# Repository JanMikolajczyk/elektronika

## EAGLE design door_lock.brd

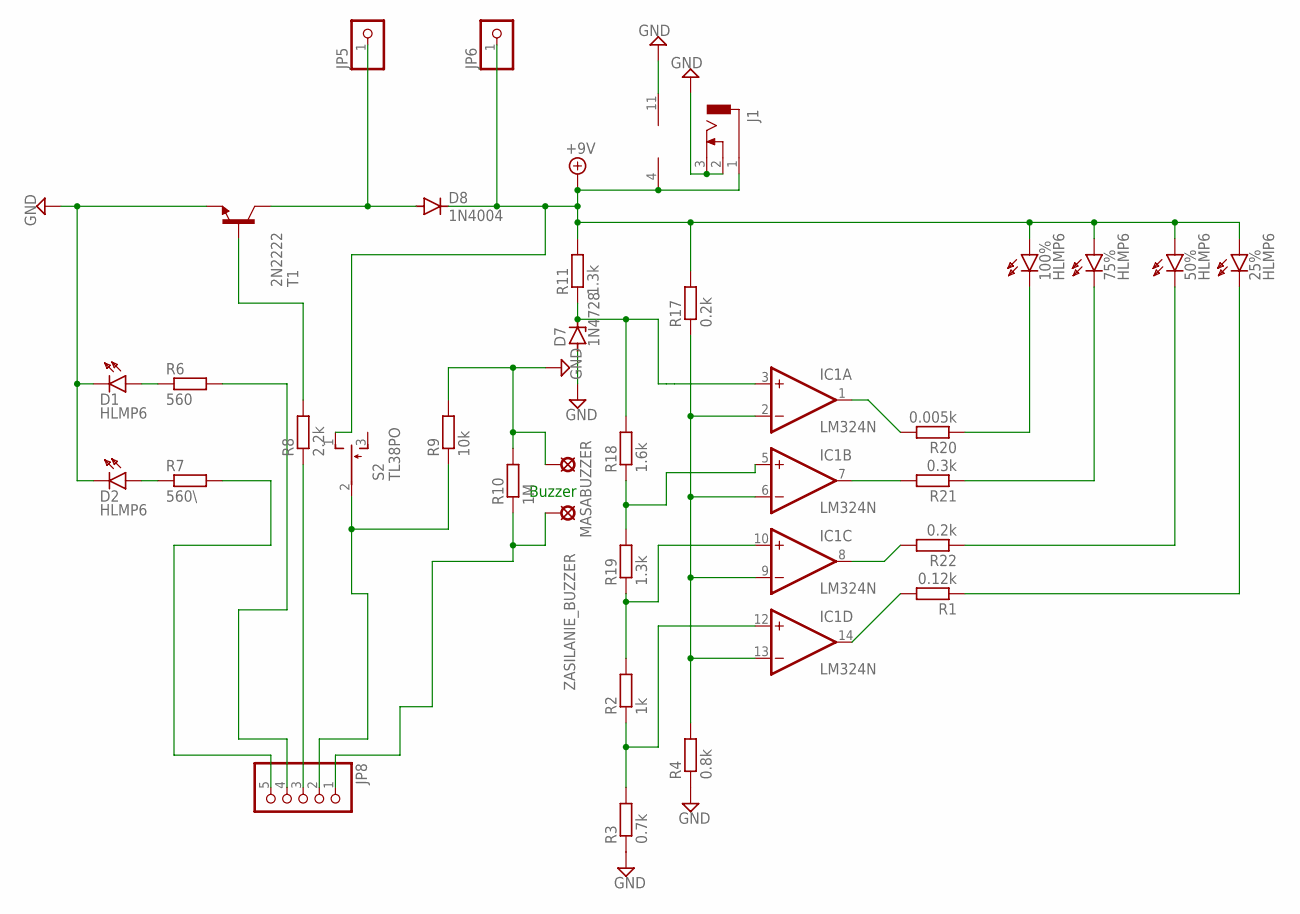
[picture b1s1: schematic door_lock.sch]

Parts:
25%, 50%, 75%, 100%: HLMP6
D1, D2: HLMP6
D7: 1N4728; DO41Z10
D8: 1N4004; DO41-10
IC1: LM324N; DIL14
J1: DCJ0303
JP5, JP6: PINHD-1X1; 1X01
JP8: PINHD-1X5; 1X05
MASABUZZER: LSP10
R1: 0.12k; 0207/10
R2: 1k; 0207/10
R3: 0.7k; 0207/10
R4: 0.8k; 0207/10
R6: 560; 0207/10
R7: 560\; 0207/10
R8: 2.2k; 0207/10
R9: 10k; 0207/10
R10: 1M; 0207/10
R11, R19: 1.3k; 0207/10
R17, R22: 0.2k; 0207/10
R18: 1.6k; 0207/10
R20: 0.005k; 0207/10
R21: 0.3k; 0207/10
S2: TL38PO; TL3XPO
T1: 2N2222; TO18
ZASILANIE_BUZZER: LSP10

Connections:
+9V: 25%.A, 50%.A, 75%.A, 100%.A, D8.C, IC1.4 (V+), J1.1, JP6.1, R11.2, R17.2, S2.1 (O)
GND: D1.K, D2.K, D7.A, IC1.11 (V-), J1.2, J1.3, MASABUZZER.MP, R3.1, R4.1, R9.2, R10.2, T1.1 (E)
unnamed: R8.2, T1.2 (B)
unnamed: D1.A, R6.1
unnamed: D2.A, R7.1
unnamed: IC1.1 (OUT), R20.2
unnamed: JP8.4, R6.2
unnamed: JP8.3, R8.1
unnamed: D8.A, JP5.1, T1.3 (C)
unnamed: IC1.7 (OUT), R21.2
unnamed: D7.C, IC1.3 (+IN), R11.1, R18.2
unnamed: IC1.5 (+IN), R18.1, R19.2
unnamed: IC1.10 (+IN), R2.2, R19.1
unnamed: IC1.12 (+IN), R2.1, R3.2
unnamed: JP8.1, R10.1, ZASILANIE_BUZZER.MP
unnamed: IC1.2 (-IN), IC1.6 (-IN), IC1.9 (-IN), IC1.13 (-IN), R4.2, R17.1
unnamed: JP8.2, R9.1, S2.2
unnamed: 75%.K, R21.1
unnamed: 50%.K, R22.1
unnamed: IC1.8 (OUT), R22.2
unnamed: IC1.14 (OUT), R1.2
unnamed: 100%.K, R20.1
unnamed: JP8.5, R7.2
unnamed: 25%.K, R1.1

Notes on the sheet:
Buzzer

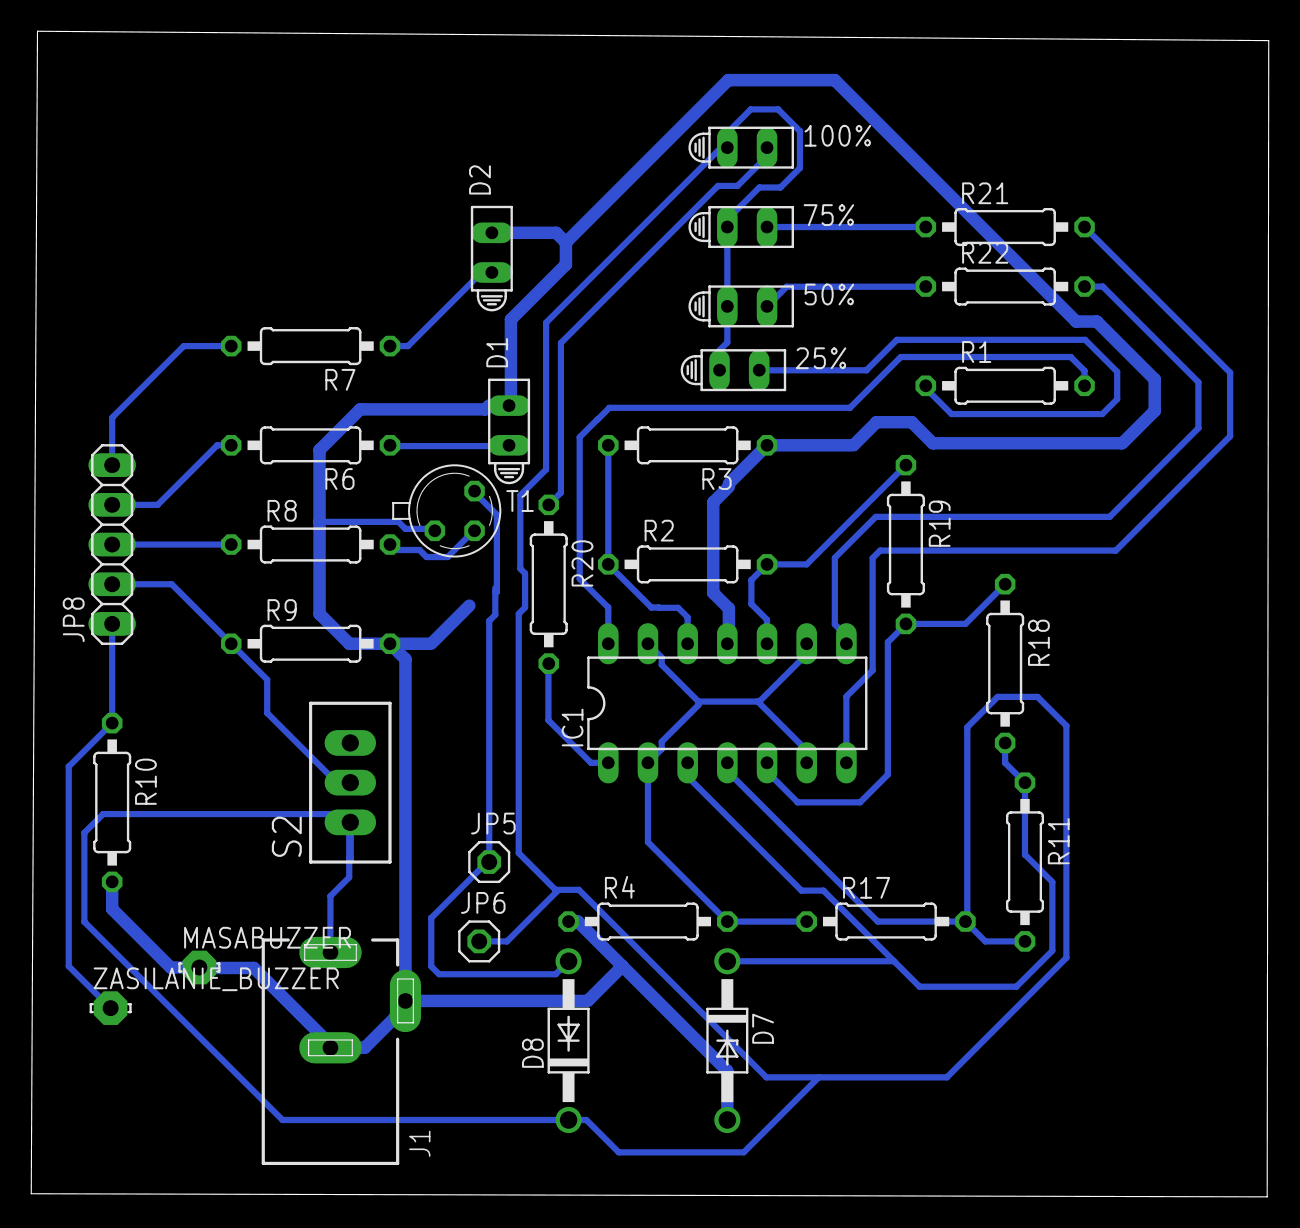
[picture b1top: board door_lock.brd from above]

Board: 2 copper layers, 79.2 x 74.6 mm, 33 parts (0 on the bottom side), 24 nets.

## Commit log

2025-06-17 Create FFT GRB LED
